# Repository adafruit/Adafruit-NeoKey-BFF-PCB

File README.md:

## Adafruit NeoKey BFF for Mechanical Key Add-On for QT Py and Xiao - For MX Compatible Switches PCB

<a href="http://www.adafruit.com/products/5695"><br/>
Click here to purchase one from the Adafruit shop</a>

PCB files for the Adafruit NeoKey BFF for Mechanical Key Add-On for QT Py and Xiao - For MX Compatible Switches. 

Format is EagleCAD schematic and board layout
* https://www.adafruit.com/product/5695

### Description

Our QT Py boards are a great way to make very small microcontroller projects that pack a ton of power - and now we have a way for you to quickly add a nice mechanical key that also can glow any color of the rainbow. 

We call this the Adafruit NeoKey BFF - a "Best Friend Forever". When you were a kid you may have learned about the "buddy" system, well this product is kinda like that! A board that will watch your QT Py's back and give it more capabilities.

This PCB is designed to fit onto the back of any QT Py or Xiao board; it can be soldered into place or use pin and socket headers to make it removable. Onboard is a Kailh socket, which means you can plug in any MX-compatible switch instead of soldering it in. You may need a little glue to keep the switch in place: hot glue or a dot of epoxy worked fine for us. Also comes with a single reverse-mount NeoPixel pointing up through the spot where many switches would have an LED to shine through.

We include some header that you can solder to your QT Py. You can also pick up an Itsy Bitsy short female header kit to make it removable but compact, you'll just need to trim down the headers to 7 pins long.

The key-switch is default connected to A3 and the NeoPixel to A2 but there are onboard jumpers you can cut to re-configure if you desire.

QT Py is not included.

Please note, each order comes with one assembled PCB and break-off header. A mechanical switch and key cap are not included! Use any MX-compatible switch: Kailh, Gateron, etc all work!

### License

Adafruit invests time and resources providing this open source design, please support Adafruit and open-source hardware by purchasing products from [Adafruit](https://www.adafruit.com)!

Designed by Limor Fried/Ladyada for Adafruit Industries.

Creative Commons Attribution/Share-Alike, all text above must be included in any redistribution. 
See license.txt for additional details.

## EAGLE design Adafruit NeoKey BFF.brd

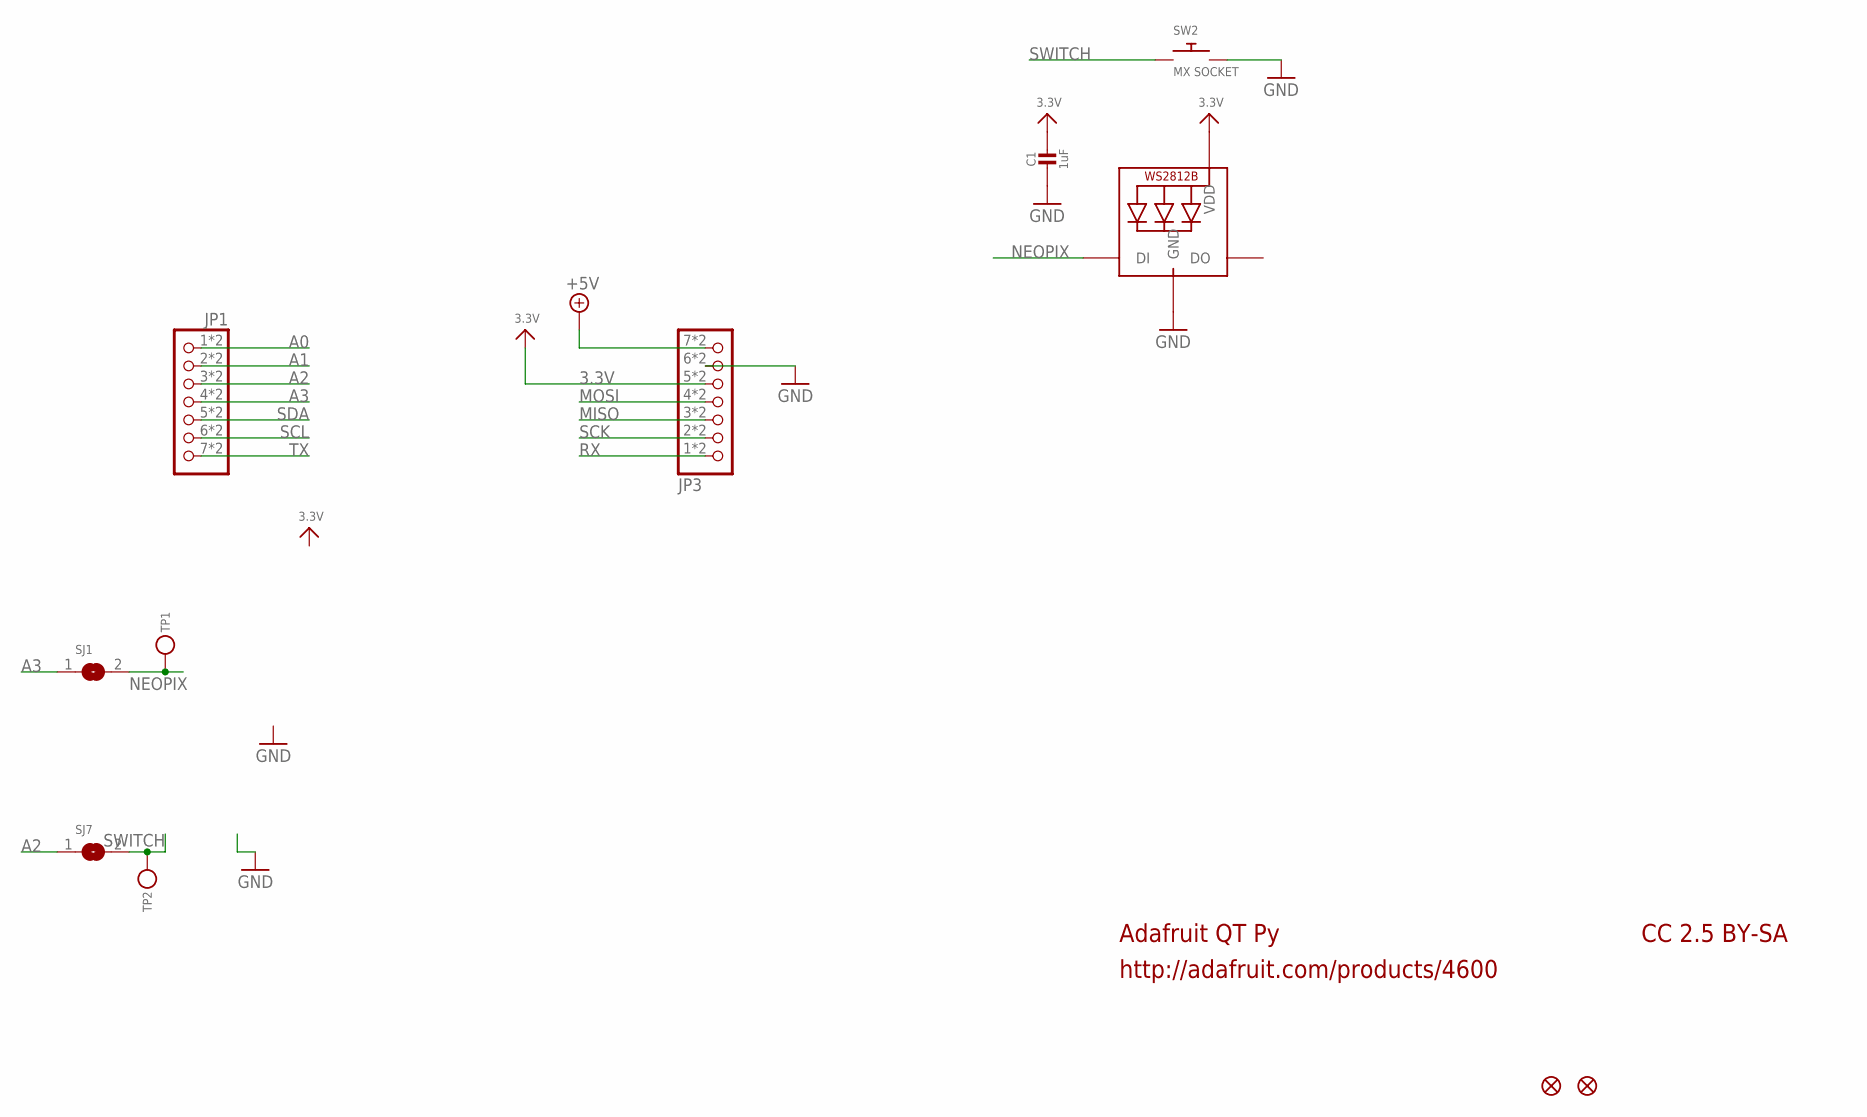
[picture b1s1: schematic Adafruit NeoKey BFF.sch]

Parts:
C1: 1uF; 0603-NO
JP1, JP3: HEADER-1X7_CASTEL; 1X07_CASTEL
LED2: WS2812B_SK6812E; NEO3535_REVERSE
SJ1, SJ7: SOLDERJUMPERCLOSED; SOLDERJUMPER_CLOSEDWIRE
SW2: MX SOCKET; KAILH_SOCKET
TP1, TP2: TESTPOINT1.5X2.0MM_NOCREAM; PAD-1.5X2.0
U$6, U$8: FIDUCIAL_1MM

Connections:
3.3V: C1.1, JP3.5, JP3.5C (5), LED2.1-VDD (VDD)
+5V: JP3.7, JP3.7C (7)
A0: JP1.1, JP1.1C (1)
A1: JP1.2, JP1.2C (2)
A2: JP1.3, JP1.3C (3), SJ7.1
A3: JP1.4, JP1.4C (4), SJ1.1
GND: C1.2, JP3.6, JP3.6C (6), LED2.3-GND (GND), SW2.2
MISO: JP3.3, JP3.3C (3)
MOSI: JP3.4, JP3.4C (4)
NEOPIX: LED2.4-DIN (DI), SJ1.2, TP1.P$1
RX: JP3.1, JP3.1C (1)
SCK: JP3.2, JP3.2C (2)
SCL: JP1.6, JP1.6C (6)
SDA: JP1.5, JP1.5C (5)
SWITCH: SJ7.2, SW2.1, TP2.P$1
TX: JP1.7, JP1.7C (7)

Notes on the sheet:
Adafruit QT Py
http://adafruit.com/products/4600
CC 2.5 BY-SA

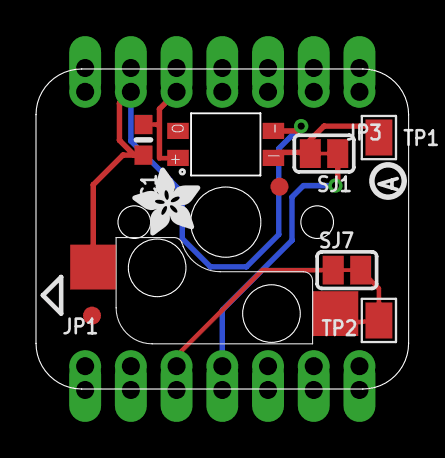
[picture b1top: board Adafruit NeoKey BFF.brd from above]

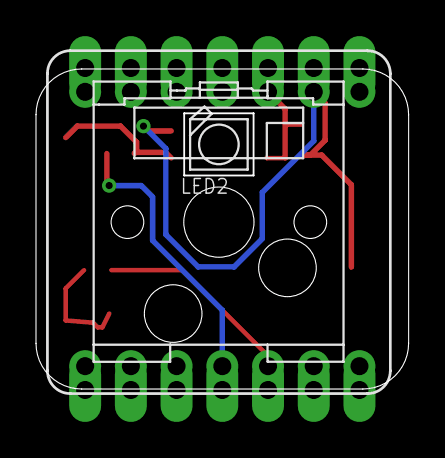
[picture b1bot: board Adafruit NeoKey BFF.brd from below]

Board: 2 copper layers, 20.7 x 17.8 mm, 23 parts (2 on the bottom side), 16 nets.

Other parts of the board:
PLABEL0: PLABEL0
PLABEL1: PLABEL1
PLABEL2: PLABEL2
PLABEL3: PLABEL3
PLABEL4: PLABEL4
PLABEL5: PLABEL5
PLABEL6: PLABEL6
PLABEL7: PLABEL7
PLABEL8: PLABEL8
PLABEL9: PLABEL9
U$2: ADAFRUIT_3.5MM
U$3: PCBFEAT-REV-040

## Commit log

2023-02-13 adding cookiecutter output

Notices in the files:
parts and their libraries:
microbuilder: This work is placed in the public domain, and may be freely used for commercial and non-commercial work with the following conditions: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
